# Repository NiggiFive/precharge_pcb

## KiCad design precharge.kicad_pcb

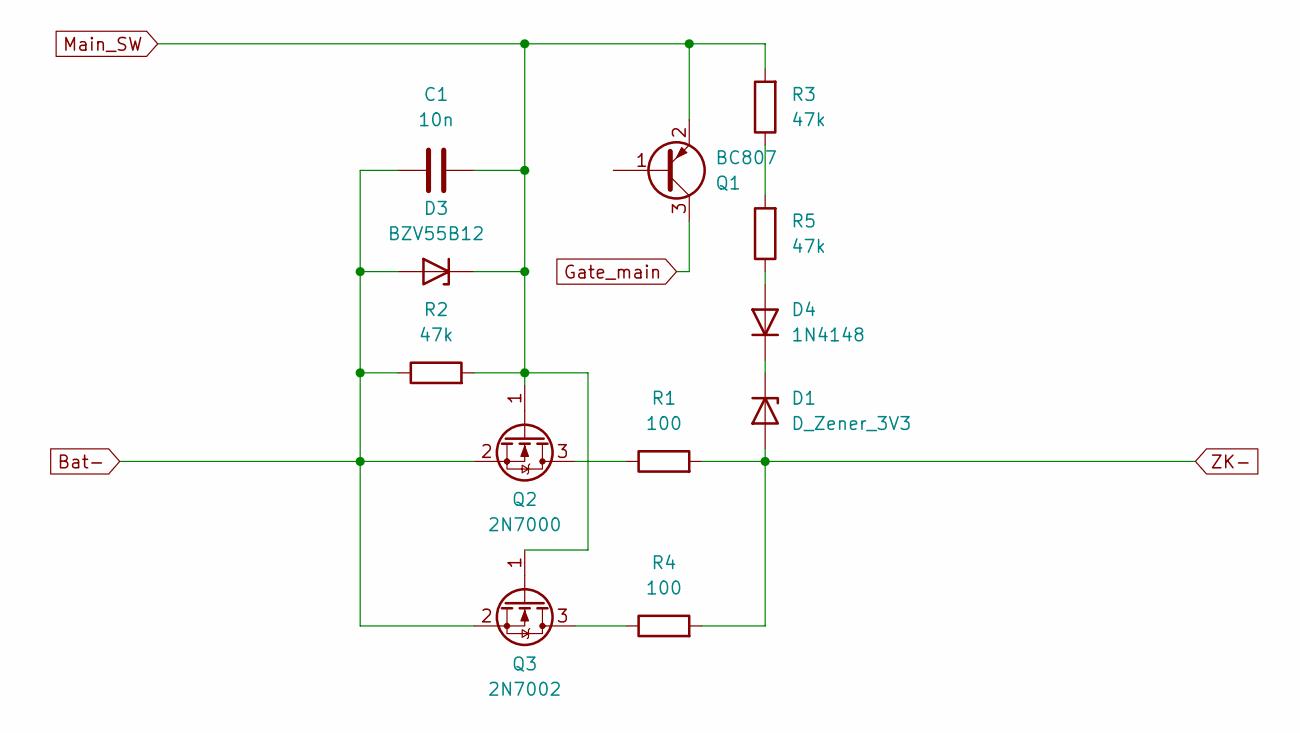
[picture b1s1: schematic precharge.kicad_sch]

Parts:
C1: 10n; C_0805_2012Metric_Pad1.18x1.45mm_HandSolder
D1: D_Zener_3V3; D_MiniMELF_Handsoldering
D3: BZV55B12; D_MiniMELF
D4: 1N4148; D_SOD-123
Q1: BC807; SOT-23
Q2: 2N7000; SOT-23
Q3: 2N7002; SOT-23
R1, R4: 100; R_Axial_DIN0207_L6.3mm_D2.5mm_P10.16mm_Horizontal
R2, R3, R5: 47k; R_0805_2012Metric_Pad1.20x1.40mm_HandSolder

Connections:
Bat-: C1.1, D3.2 (A), Q2.2 (S), Q3.2 (S), R2.1
Gate_main: Q1.3 (C)
Main_SW: C1.2, D3.1 (K), Q1.2 (E), Q2.1 (G), Q3.1 (G), R2.2, R3.2
unnamed: D1.1 (K), D4.1 (K)
unnamed: D4.2 (A), R5.1
unnamed: Q2.3 (D), R1.1
unnamed: Q3.3 (D), R4.1
unnamed: R3.1, R5.2
ZK-: D1.2 (A), R1.2, R4.2

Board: 2 copper layers, 12 parts (0 on the bottom side), 8 nets, no tracks yet.

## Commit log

2024-08-31 echtes pcb
